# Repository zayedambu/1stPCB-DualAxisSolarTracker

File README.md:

# 1stPCB-DualAxisSolarTracker
This repository documents my first steps into the exciting world of Printed Circuit Board (PCB) design using KiCad. Inspired by my previous Arduino-based dual-axis solar tracking system (which, let's be honest, was a glorious wire mess 😅), 
I decided to dedicate my college break to learning how to create professional-looking and functional circuits.

🚀 What's Inside?

This project captures my learning journey through the fundamental stages of PCB design:

Schematic Design: The logical representation of the circuit, detailing how components are connected.

Footprint Assignment: Mapping physical component dimensions to the schematic symbols.

PCB Layout & Routing: The art of placing components and drawing the copper traces that connect them on the board.

It's been a really interesting day, full of discoveries and problem-solving!

🛠️ Tools Used
KiCad: The open-source EDA suite used for designing the PCB.

💡 Rookie Mistakes & Open for Suggestions!
As this is my very first dive into KiCad and formal PCB design, I'm sure there are plenty of rookie mistakes, design rule violations, and unconventional choices lurking within these files!

I am completely open to all feedback and suggestions. My goal is to learn and improve, and there's no better way than to share and get insights from experienced folks. Please feel free to open issues, submit pull requests, or just drop a comment with your thoughts!

Let's learn together!

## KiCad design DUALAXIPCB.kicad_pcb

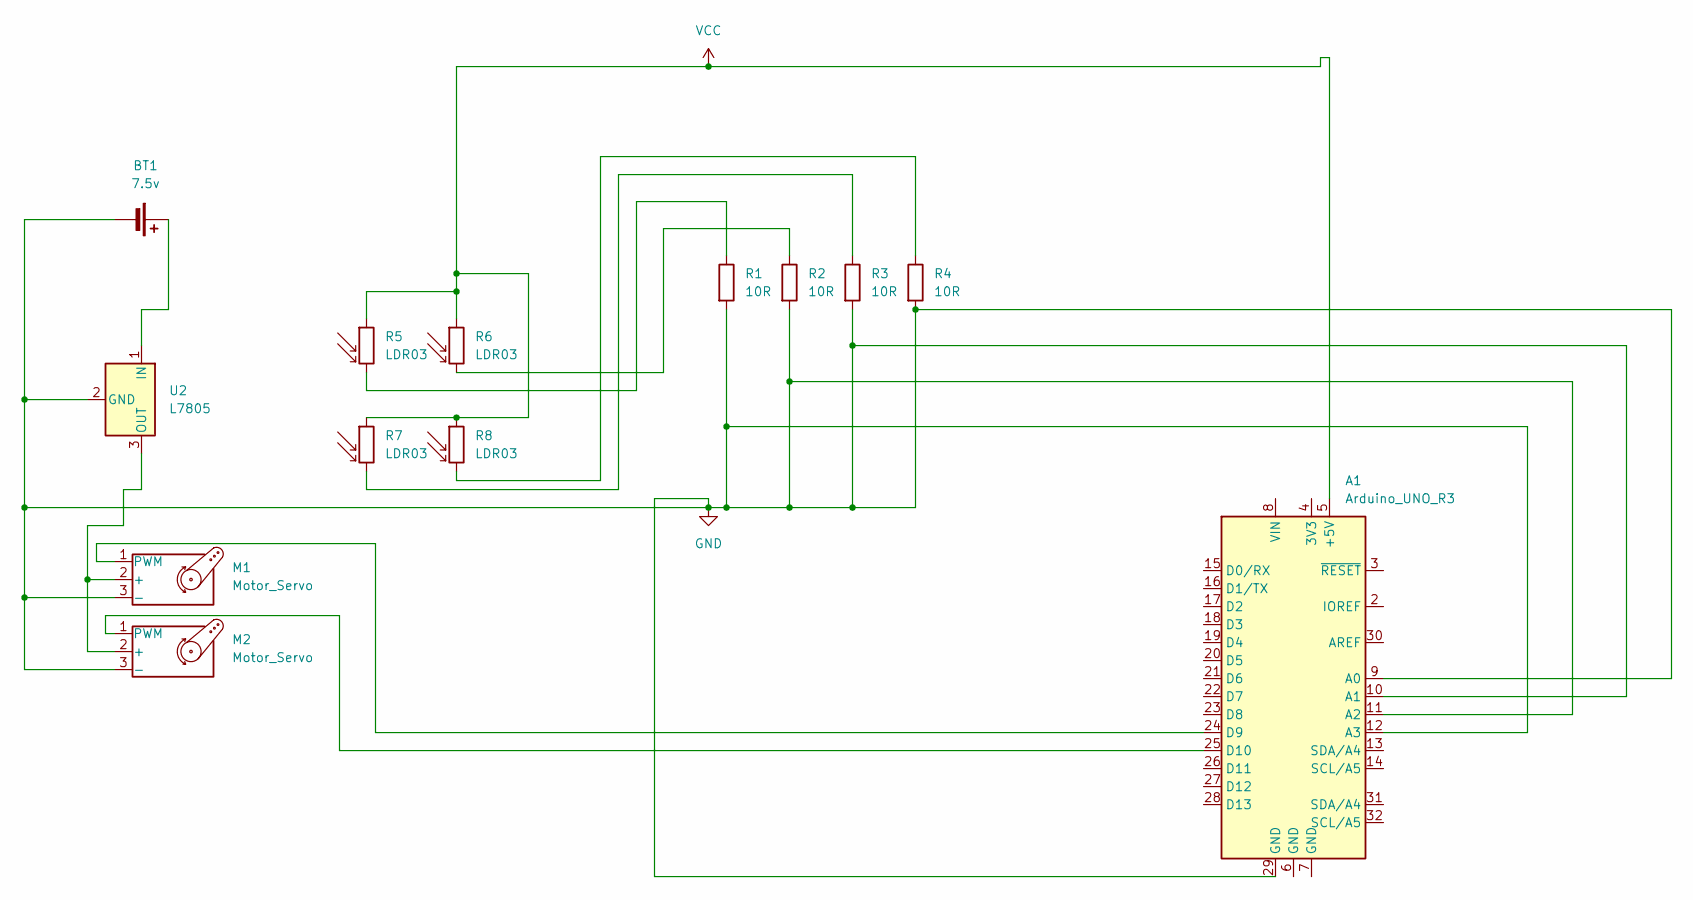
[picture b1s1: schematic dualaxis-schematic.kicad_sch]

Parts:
A1: Arduino_UNO_R3
BT1: 7.5v; Battery_Panasonic_CR2025-V1AK_Vertical_CircularHoles
M1, M2: Motor_Servo; SERVO
R1, R2, R3, R4: 10R; R_Axial_DIN0516_L15.5mm_D5.0mm_P20.32mm_Horizontal
R5, R6, R7, R8: LDR03; R_LDR_10x8.5mm_P7.6mm_Vertical
U2: L7805; L7805 5v

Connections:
GND: A1.9 (A0), A1.10 (A1), A1.11 (A2), A1.12 (A3), A1.29 (GND), BT1.2 (-), M1.3 (-), M2.3 (-), R1.2, R2.2, R3.2, R4.2, U2.2 (GND)
unnamed: A1.24 (D9), M1.1 (PWM)
unnamed: A1.25 (D10), M2.1 (PWM)
unnamed: BT1.1 (+), U2.1 (IN)
unnamed: M1.2 (+), M2.2 (+), U2.3 (OUT)
unnamed: R1.1, R5.2
unnamed: R2.1, R6.2
unnamed: R3.1, R7.2
unnamed: R4.1, R8.2
VCC: A1.5 (+5V), R5.1, R6.1, R7.1, R8.1

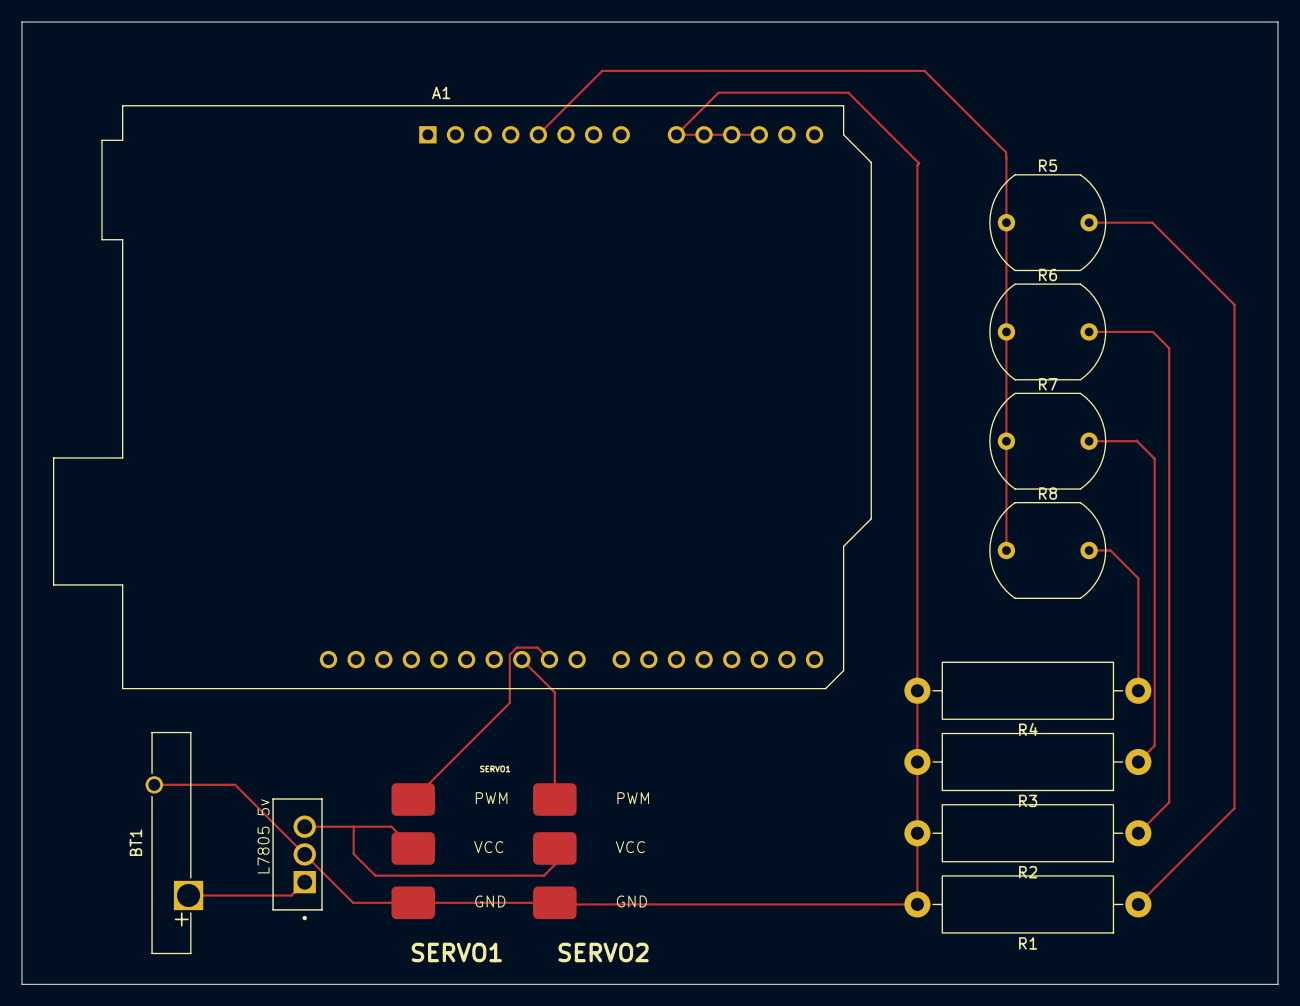
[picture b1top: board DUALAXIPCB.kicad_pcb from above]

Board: 2 copper layers, 115.5 x 88.5 mm, 13 parts (0 on the bottom side), 10 nets.
